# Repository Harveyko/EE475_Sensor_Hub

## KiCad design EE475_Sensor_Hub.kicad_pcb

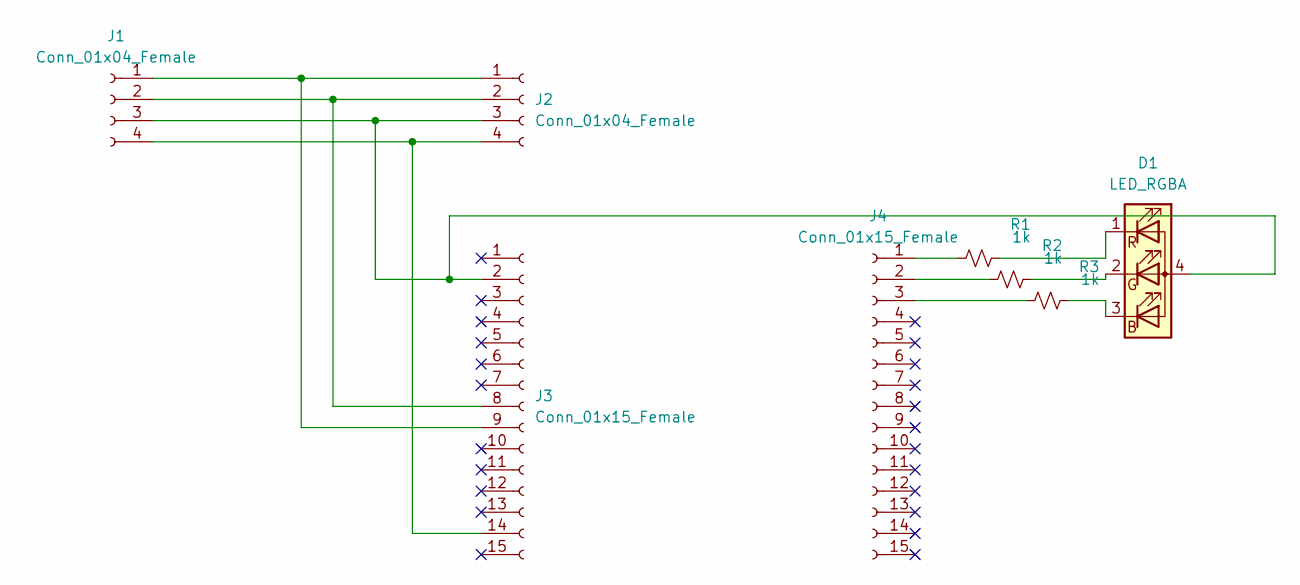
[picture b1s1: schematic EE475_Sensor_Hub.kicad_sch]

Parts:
D1: LED_RGBA; LED_RGB_1210
J1, J2: Conn_01x04_Female; PinSocket_1x04_P2.54mm_Vertical
J3, J4: Conn_01x15_Female; PinSocket_1x15_P2.54mm_Vertical
R1, R2, R3: 1k; R_1206_3216Metric

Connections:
unnamed: D1.1 (RK), R1.2
unnamed: D1.2 (GK), R2.2
unnamed: D1.3 (BK), R3.2
unnamed: D1.4 (A), J1.3, J2.3, J3.2
unnamed: J1.1, J2.1, J3.9
unnamed: J1.2, J2.2, J3.8
unnamed: J1.4, J2.4, J3.14
unnamed: J4.1, R1.1
unnamed: J4.2, R2.1
unnamed: J4.3, R3.1

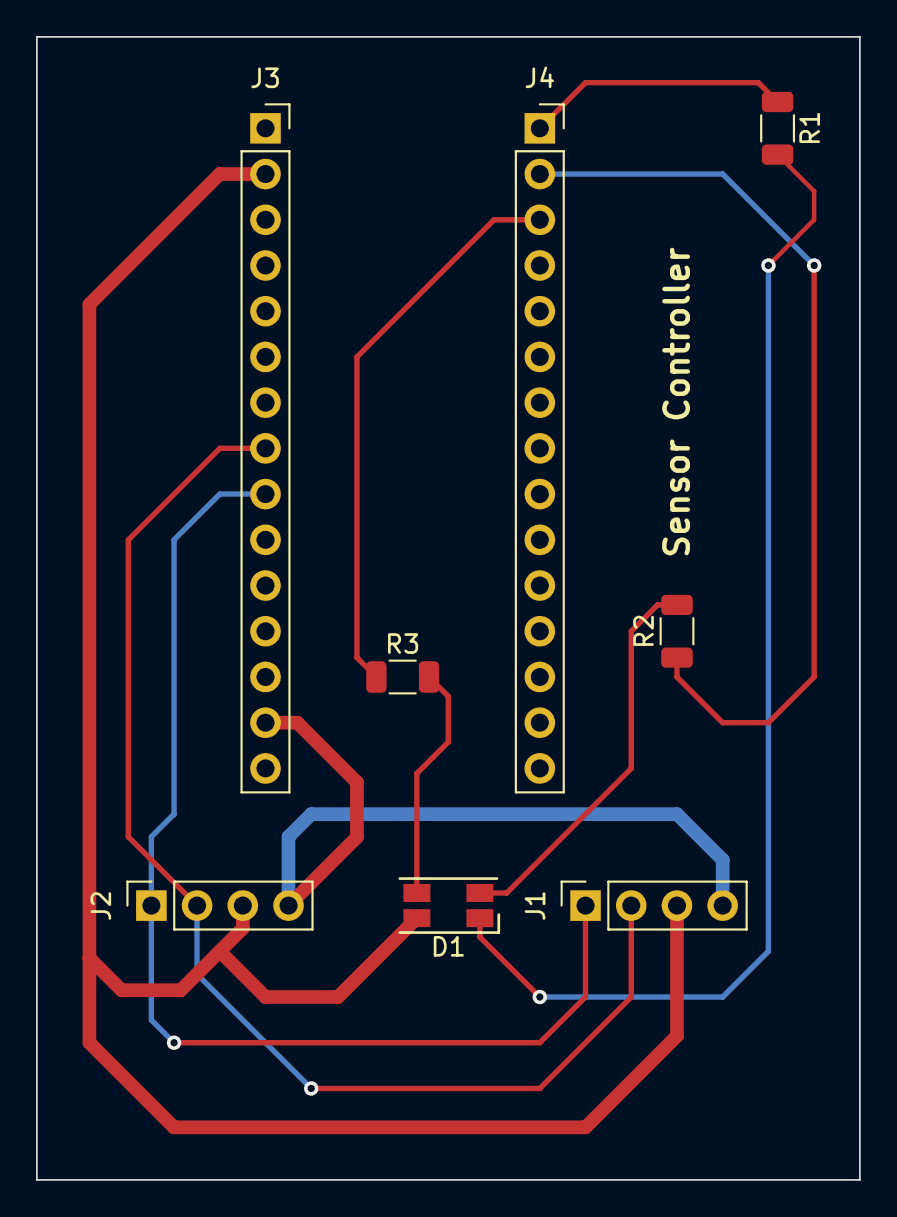
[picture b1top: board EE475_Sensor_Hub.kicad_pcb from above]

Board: 2 copper layers, 45.7 x 63.5 mm, 8 parts (0 on the bottom side), 10 nets.

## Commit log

2022-11-11 Finish the PCB trace and pass the Design rule checker
2022-11-15 Final design of the PCB baord for Sensor Controller
2022-11-16 Updated version of the PCB based on professor and TAs feedback
2022-11-18 Modify LED and resistor footprint
